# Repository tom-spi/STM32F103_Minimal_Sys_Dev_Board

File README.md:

# STM32F103_Minimal_Sys_Dev_Board

A minimal system STM32F103 based development board. All Major communication interfaces broken out. USB 2.0 device support. Complete with 3.3V regulator & 16MHz external crystal.
All I/O pins broken out onto headers & an SWD Header for programming. 
Boards manufactured and assembled by JLCPCB.

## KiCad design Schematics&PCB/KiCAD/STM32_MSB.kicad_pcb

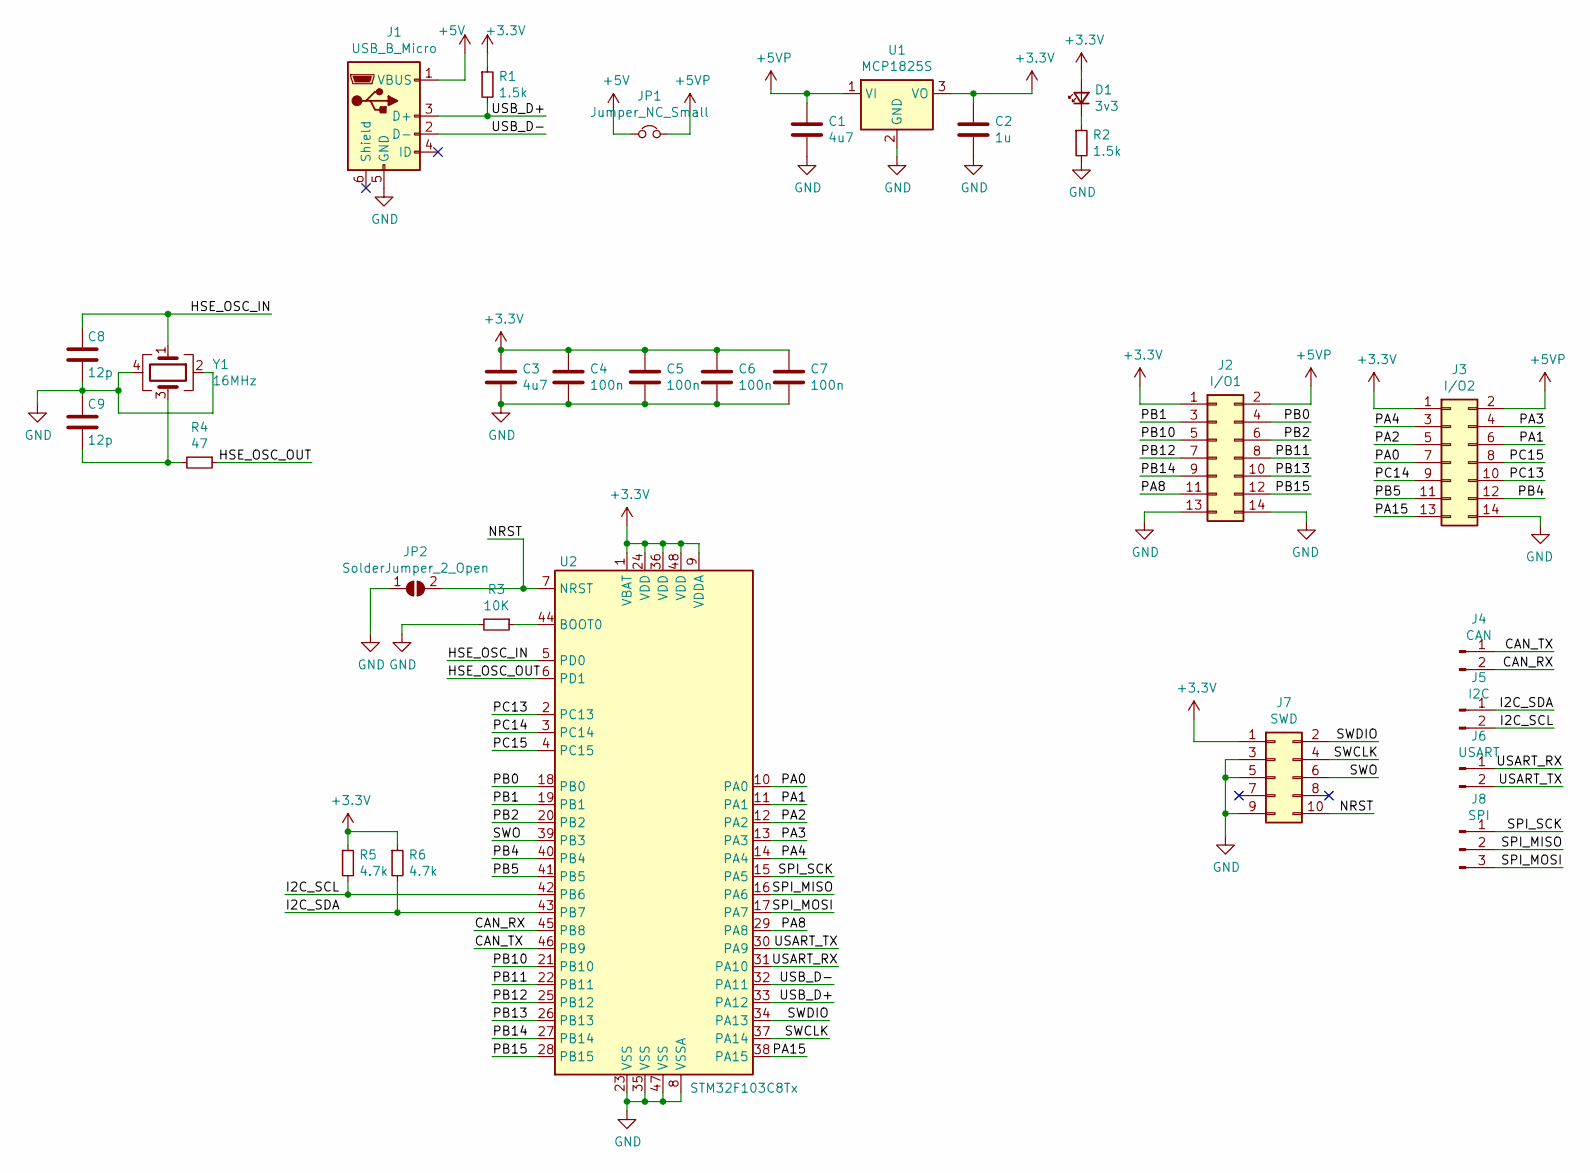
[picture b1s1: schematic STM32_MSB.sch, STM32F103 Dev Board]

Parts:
C1, C3: 4u7; C_0603_1608Metric; LCSC C19666
C2: 1u; C_0603_1608Metric; LCSC C15849
C4, C5, C6, C7: 100n; C_0603_1608Metric; LCSC C14663
C8, C9: 12p; C_0603_1608Metric; LCSC C38523
D1: 3v3; C_0805_2012Metric; LCSC C2297
J1: USB_B_Micro; USB_Mini-B_Wuerth_65100516121_Horizontal; LCSC C91144
J2: I/O1; PinHeader_2x07_P2.54mm_Vertical
J3: I/O2; PinHeader_2x07_P2.54mm_Vertical
J4: CAN; PinHeader_1x02_P2.54mm_Vertical
J5: I2C; PinHeader_1x02_P2.54mm_Vertical
J6: USART; PinHeader_1x02_P2.54mm_Vertical
J7: SWD; PinHeader_2x05_P2.54mm_Vertical
J8: SPI; PinHeader_1x03_P2.54mm_Vertical
JP1: Jumper_NC_Small; PinHeader_1x02_P2.54mm_Vertical
JP2: SolderJumper_2_Open; SolderJumper-2_P1.3mm_Open_RoundedPad1.0x1.5mm
R1, R2: 1.5k; R_0603_1608Metric; LCSC C22843
R3: 10K; R_0603_1608Metric; LCSC C25804
R4: 47; R_0603_1608Metric; LCSC C23182
R5, R6: 4.7k; R_0603_1608Metric; LCSC C23162
U1: MCP1825S; SOT-223-3_TabPin2
U2: STM32F103C8Tx; LQFP-48_7x7mm_P0.5mm; LCSC C8734
Y1: 16MHz; Crystal_SMD_3225-4Pin_3.2x2.5mm; LCSC C13738

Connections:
+3V3: C2.1, C3.1, C4.1, C5.1, C6.1, C7.1, D1.2 (A), J2.1, J3.1, J7.1, R1.1, R5.1, R6.1, U1.3 (VO), U2.1 (VBAT), U2.9 (VDDA), U2.24 (VDD), U2.36 (VDD), U2.48 (VDD)
+5V: J1.1 (VBUS), JP1.1
+5VP: C1.1, J2.2, J3.2, JP1.2, U1.1 (VI)
/CAN_RX: J4.2, U2.45 (PB8)
/CAN_TX: J4.1, U2.46 (PB9)
/HSE_OSC_IN: C8.1, U2.5 (PD0), Y1.1
/HSE_OSC_OUT: R4.1, U2.6 (PD1)
/I2C_SCL: J5.2, R5.2, U2.42 (PB6)
/I2C_SDA: J5.1, R6.2, U2.43 (PB7)
/NRST: J7.10, JP2.2 (B), U2.7 (NRST)
/PA0: J3.7, U2.10 (PA0)
/PA1: J3.6, U2.11 (PA1)
/PA2: J3.5, U2.12 (PA2)
/PA3: J3.4, U2.13 (PA3)
/PA4: J3.3, U2.14 (PA4)
/PA8: J2.11, U2.29 (PA8)
/PA15: J3.13, U2.38 (PA15)
/PB0: J2.4, U2.18 (PB0)
/PB1: J2.3, U2.19 (PB1)
/PB2: J2.6, U2.20 (PB2)
/PB4: J3.12, U2.40 (PB4)
/PB5: J3.11, U2.41 (PB5)
/PB10: J2.5, U2.21 (PB10)
/PB11: J2.8, U2.22 (PB11)
/PB12: J2.7, U2.25 (PB12)
/PB13: J2.10, U2.26 (PB13)
/PB14: J2.9, U2.27 (PB14)
/PB15: J2.12, U2.28 (PB15)
/PC13: J3.10, U2.2 (PC13)
/PC14: J3.9, U2.3 (PC14)
/PC15: J3.8, U2.4 (PC15)
/SPI_MISO: J8.2, U2.16 (PA6)
/SPI_MOSI: J8.3, U2.17 (PA7)
/SPI_SCK: J8.1, U2.15 (PA5)
/SWCLK: J7.4, U2.37 (PA14)
/SWDIO: J7.2, U2.34 (PA13)
/SWO: J7.6, U2.39 (PB3)
/USART_RX: J6.1, U2.31 (PA10)
/USART_TX: J6.2, U2.30 (PA9)
/USB_D+: J1.3 (D+), R1.2, U2.33 (PA12)
/USB_D-: J1.2 (D-), U2.32 (PA11)
GND: C1.2, C2.2, C3.2, C4.2, C5.2, C6.2, C7.2, C8.2, C9.1, J1.5 (GND), J2.13, J2.14, J3.14, J7.3, J7.5, J7.9, JP2.1 (A), R2.2, R3.2, U1.2 (GND), U2.8 (VSSA), U2.23 (VSS), U2.35 (VSS), U2.47 (VSS), Y1.2, Y1.4
unnamed: C9.2, R4.2, Y1.3
unnamed: D1.1 (K), R2.1
unnamed: R3.1, U2.44 (BOOT0)

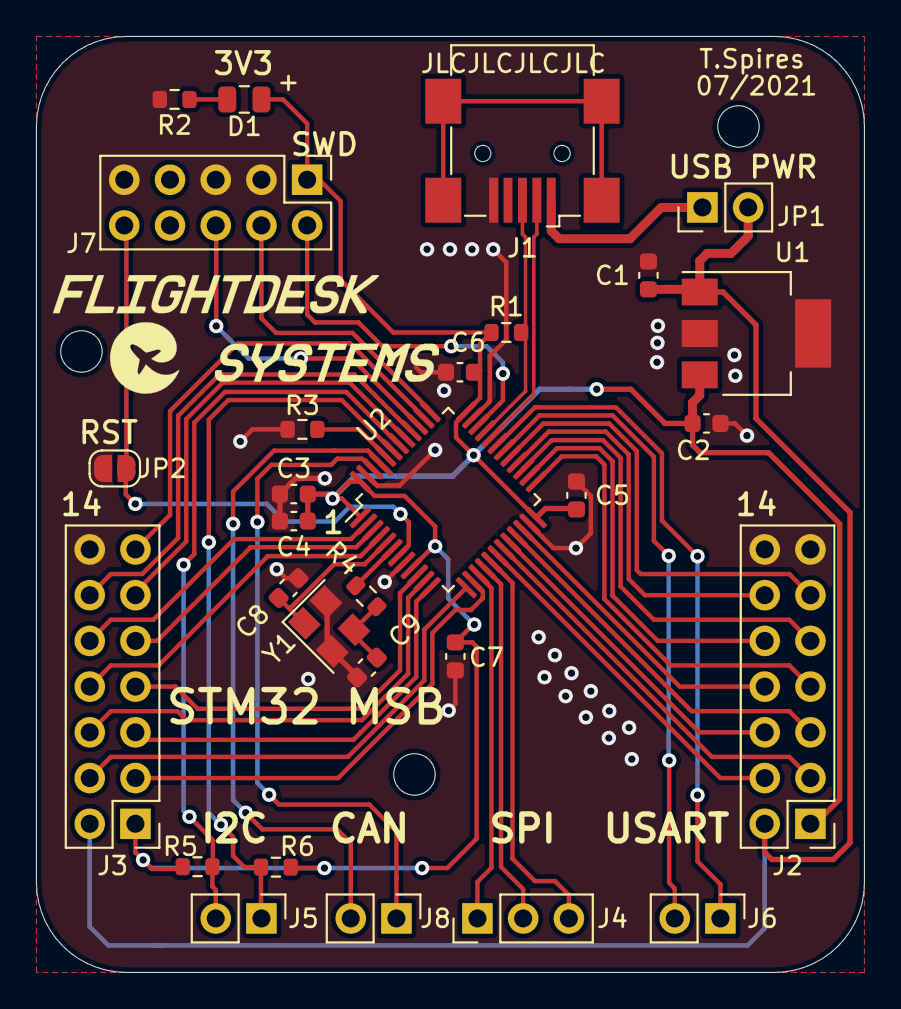
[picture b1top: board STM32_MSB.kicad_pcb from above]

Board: 2 copper layers, 46.0 x 52.0 mm, 29 parts (0 on the bottom side), 45 nets.
